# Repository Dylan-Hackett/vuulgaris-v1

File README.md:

# Vuulgaris V1

A 4-channel sample-scrubbing instrument. Long capacitive copper pads on a PCB faceplate
represent the length of a waveform; dragging a finger along a pad scrubs through the sample.
Each track carries a swappable machine that is either a sampler or a synth, with Plaits as
the synth engine.

```
[ FACEPLATE PCB ]
  4x capacitive pads, ~216mm (length follows the inter-pad gap, Q17)
  MSP430FR2675TPTR (CapTIvate touch MCU) on the back side
        |
        |  UART (primary) or I2C (fallback), + IRQ, + BSL entry lines
        v
[ MAIN PCB ]
  Daisy Patch SM (STM32H750) - audio engine, sample playback, UI
  microSD socket
  2.42" SSD1309 OLED (SPI)
  Rotary encoder
  Stereo Buchla-style low pass gate (analog)
```

## Layout

| Folder | Contents |
|---|---|
| [`docs/`](docs/) | `design-state.md` (source of truth), ADRs, open questions, pin allocation, panel budget |
| [`mockups/`](mockups/) | Parametric comb pad generator, Salamis faceplate reference + dimensioned |
| [`datasheets/`](datasheets/) | Manifest, fetch script and the datasheet PDFs. |
| [`hardware/`](hardware/) | Faceplate and main PCB, gerbers, BOM spreadsheet |
| [`fw-daisy/`](fw-daisy/) | Daisy Patch SM firmware. libDaisy + DaisySP as submodules. |
| [`fw-touch/`](fw-touch/) | MSP430FR2675 firmware. CCS + CapTIvate Design Center. |

## Start here

1. **[docs/design-state.md](docs/design-state.md)** is authoritative. Everything else is
   derived from it.
2. **[docs/notes/next-steps.md](docs/notes/next-steps.md)** step 0 is the thing to do first,
   and it is deliberately cheap: one 2-layer board with **two pads in final tooth geometry**,
   roughly $50 and 2 weeks. It answers whether a moving finger reads and repeats cleanly, and
   the second pad settles the inter-pad gap, which sets the size of the whole instrument.
3. **[docs/pin-allocation.md](docs/pin-allocation.md)** is resolved and safe to lay out
   against. Zero spare bidirectional GPIO, so any addition means a removal.
4. **[docs/panel-budget.md](docs/panel-budget.md)** is **not** settled, and it hinges on one
   measurement. The Salamis composition locks `pad length = 12 x pad pitch`, so the inter-pad
   gap ([Q17](docs/notes/open-questions.md)) sets the size of the whole instrument: a 6mm gap
   gives a 298 x 154mm panel with 216mm pads, a 10mm gap gives 365 x 189mm with 264mm pads.
5. **[docs/notes/open-questions.md](docs/notes/open-questions.md)** lists what is still
   unverified. Only one is a real design risk: **Q1**, whether a moving finger on bare copper
   reads and repeats cleanly. **Q10, Q13, Q15, Q18** are bench or datasheet checks. **Q17**
   (inter-pad gap) sets the instrument size. **Q7** is a cash decision.

## Setup

```bash
# Firmware submodules
git -C fw-daisy submodule update --init --recursive
cd fw-daisy && make libs && make

# Datasheets are committed; this re-fetches any that are missing
cd datasheets && ./fetch-datasheets.sh
```

## The three facts that shape everything else

**The MCU is on the faceplate, not the main board.** TI's design guide says keep
MCU-to-electrode traces as short as possible and explicitly warns against routing capacitive
sensing lines through board-to-board connectors or cables. That is what forces the two-board
split, and only ~8-10 digital pins cross between them.

**Accuracy is not the requirement. Monotonicity and continuity are.** You scrub by listening
and adjusting, so the loop closes through your ears and absolute position error is inaudible.
A bent curve is a lookup table. What cannot be fixed downstream is a **momentary reversal**
(sample stutters backward) or a **dropout** (click). Scan rate and jitter at rest are both
settled, see [Q1](docs/notes/open-questions.md). This is where the Trautonium pivot changed
the requirements: there, position was pitch and a 2% error was a wrong note.

**Electrode order is generated first, then laid out.** `RX0->E00, RX1->E01, RX2->E02,
RX3->E03`, produced in Design Center **before** the PCB. A swapped pair gives garbage
interpolation on a board that passes every electrical check.

**Every pot past the eighth costs a bidirectional GPIO.** CV_1-CV_8 are input-only pins that
can do nothing else, so the first 8 are free. Pots 9-12, the envelope attack and release for
each stereo side, take A2, A3, D8 and D9, and that consumes all 16 bidirectional GPIO exactly.
A 13th is impossible.

**Patch SM has two USB ports, and only one of them is on the header.** DFU flashing and USB
MIDI run on the module's own onboard Micro USB (PA11/PA12). **A8/A9 are a separate USB host
port**, spent here on IO. The cost is that USB access means unscrewing the module from the
rack; firmware ships via SD card instead.

## Decisions already made

| # | Decision |
|---|---|
| [0001](docs/decisions/0001-pivot-to-capacitive-scrubbing.md) | Pivot from Trautonium analog to capacitive sample-scrubbing |
| [0002](docs/decisions/0002-msp430fr2675-for-touch.md) | MSP430FR2675 (CapTIvate) for touch sensing |
| [0003](docs/decisions/0003-comb-pad-rx0-wraparound.md) | Comb-tooth pads with RX0 wraparound |
| [0004](docs/decisions/0004-no-overlay-exposed-copper.md) | Exposed copper, no overlay, ENIG |
| [0005](docs/decisions/0005-bsl-over-daisy-uart.md) | Daisy flashes the MSP430 over BSL |
| [0006](docs/decisions/0006-ssd1309-oled.md) | 2.42" SSD1309 over SPI |
| [0007](docs/decisions/0007-buchla-lpg-over-serge-vcfq.md) | Buchla-style LPG, not Serge VCFQ |
| [0008](docs/decisions/0008-boot-sram-not-qspi.md) | BOOT_SRAM, QSPI reserved for samples |
| [0009](docs/decisions/0009-io-plan-12-adc.md) | IO plan: 12 ADC, no mux, 1-bit SD, no panel USB |

## Cost

**$162.40 at qty 1** per [the BOM](hardware/bom/vuulgaris-v1-bom.xlsx), of which **$48.76 is
confirmed** against real listings and the rest is estimated. Inside the $125-200 range in
design-state section 10.

**The enclosure is not in that number.** The prior design was CNC walnut. It is cost lever
number 3 and currently unbounded.

Stock warnings that matter: **MSP430FR2675 has 10 units at LCSC**, and the **SSD1309 has 27**.
Both are prototype quantities.

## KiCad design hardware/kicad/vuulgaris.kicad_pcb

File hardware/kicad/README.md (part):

# Vuulgaris V1 — KiCad project (main PCB)

**Migrated from EasyEDA 2026-08-16.** Schematic connectivity is generated from a
declarative netlist and verified against KiCad's own netlister. Requires KiCad 7.

```
vuulgaris.kicad_sch   69 components, 217 connections, 66 nets — VERIFIED 217/217
vuulgaris.kicad_pcb   284.3 x 125.0mm on Edge.Cuts
lib/                  symbols + footprints (see below)
tools/                the generator and the netlist it generates from
```

## Why this exists

The EasyEDA version was abandoned after its API repeatedly reported success for
writes it had not performed — `deleteBoard` returning true having deleted nothing,
`importChanges` returning true and doing nothing, wires created at exact pin
coordinates that the netlister then refused to bind. It produced a board where
**`P3V3_DAISY` was shorted to `I2C_SDA` across 9 pads** and both LDO outputs sat on
GND, and no ERC would flag any of it, because every one of those is an electrically
legal connection. It was only ever caught by diffing pad nets against an explicit
intended map.

KiCad's design is a text file. A write either happens or raises. That is the whole
reason for the move.

## The verification loop

This is the thing worth preserving. `tools/netmap.json` is the **intent**: every
pin that carries a net, taken from `docs/pin-allocation.md`. The check is:

```bash
python3 tools/mksch.py && python3 tools/netcheck.py
```

`mksch.py` is the drawing engine; the design it draws — which symbol each ref uses,
where it sits on the sheet, which footprint it gets — is `tools/design.py`. They were
one file until 2026-09-27, when the faceplate needed the same engine. The loop tools
(`mksch`, `netcheck`, `drc`, `boardcheck`, `ksym`) all take `--project faceplate`;
`tools/proj.py` says where each project keeps what.

`netcheck.py` exports the netlist with `kicad-cli` — KiCad's own code, not a
reimplementation — and diffs every `(ref, pin) -> net` both ways. The reverse
direction is the one that matters: a pin KiCad bound to a net that `netmap.json`
never asked for is exactly the `P3V3_DAISY`-shorted-to-`I2C_SDA` failure above,
and no ERC will ever flag it. **Re-run it after any change.**

Then, before plotting fab files:

```bash
python3 tools/place.py --check && python3 tools/gerbercheck.py
```

And the one that has the last word on clearance:

```
python3 tools/drc.py
```

`drc.py` runs **KiCad's own DRC** through `pcbnew.WriteDRCReport`, because
`kicad-cli` in 7.0.8 cannot. It fails on anything the project settings call an
ERROR and merely counts WARNINGs, of which this board has ~270 silkscreen ones
that JLC clips at plot time.

`boardcheck.py` is still worth running — it is fast and it checks parity
against `netmap.json`, which DRC knows nothing about — but it is no longer the
authority on clearance. It reimplemented the geometry and got the X-crossing
case wrong, so two tracks lying on top of each other on `/LPG_LED` and
`/LPG_LEDK` measured 0.6mm apart and it reported the board clean for days.
Pcbnew found them in a second.
```

## Libraries

| Library | Source | Notes |
|---|---|---|
| `lib/vuulgaris.kicad_sym` + `.pretty` | `easyeda2kicad` from LCSC part numbers | Same geometry as the EasyEDA parts, not a reinterpretation |
| `lib/daisy_es.kicad_sym` | [GregBurns/sm_kicad](https://github.com/GregBurns/sm_kicad) | Daisy Patch SM **plus** a Eurorack kit — jacks, toggles, pots, LEDs, power symbols |

Adding a part:

```bash
easyeda2kicad --full --output lib/vuulgaris --lcsc_id CXXXXXXX
```

**The Daisy symbol here has all 40 pins including A7 (GND).** The EasyEDA community
symbol was missing A7 entirely, which passes ERC silently — a pin that does not
exist cannot be reported unconnected. That defect does not exist in this project.

**Footprint format caveat:** easyeda2kicad writes the legacy `(module ...)` form.
KiCad converts it correctly when loading from the library, but it cannot be pasted
raw into a `.kicad_pcb`. Pull footprints in via Update PCB from Schematic, not by
editing the board file.

## Placement

Two kinds of position, governed differently:

| | Governed by | Move it in Pcbnew? |
|---|---|---|
| **Panel parts** (20) | the faceplate artwork | reverted, and reported — a knob has to come through its hole |
| **Free parts** (23) | you | kept. `place.py` re-reads them every run |

So: **drag the free parts around in Pcbnew, save, and they stay put.** Their
positions are recorded in `tools/free-placement.json` so the layout shows up in a
diff. A part missing from that file is new — it just arrived via F8 — and gets
seeded once from `FREE_SEED`, then the board owns it. `--reset` throws away free
moves and goes back to the seed.

Panel-facing parts are **derived, not chosen** — their coordinates come from
`hardware/placement-panel-facing.txt`, itself generated by
`mockups/generate-faceplate.py --placement`. KiCad PCB space is Y-down and native
millimetres, the same convention as that file, so the only transform is the origin
shift:

```
pcb_mm = panel_mm - (6.995, 7.000)
```

**Footprint origin is not the shaft.** What must line up with a faceplate hole is
the shaft axis, and for three of these parts that sits away from the origin:

| Part | Footprint | Shaft / centre at | Evidence |
|---|---|---|---|
| ENC1-ENC10 | `SW-TH_EC12EXXXX` | `(0, -3.75)` | silk body centre **and** both mounting lugs |
| ENC0 | `SW-TH_ALPS_EC11L1525G01` | `(0, -0.20)` | bushing circle r 4.00 |
| RV1-RV6 | `RES-ADJ-TH_RK09L1240A12` (dual-gang, Alpha `RD902F` fitted) | `(0, -5.00)` — but **placed** at `(0, -4.83)`, see `place.py` | on the tab-slot line: the ALPS RK09L and Alpha RD902F drawings |
| SW4-SW9 | `KEY-TH_4P-L12.0-W12.0-P5.00-LS12.5` (12x12 tactile) | `(0, 0)` | pads symmetric about the origin |
| DS1 | `LCD-TH_HS242L01W4S01` | header, mid of the left edge | (folded into `PANEL`) |

Placing those by origin puts the knob 4-5mm off its hole, which nothing downstream
would flag. `ORIGIN_OFFSET` in `place.py` carries the correction.

**Only ENC0 and the pots have a bushing circle to key off.** The EC12 has none —
its only circles are four r=0.9 pad drill markers, and treating the largest of
those as a shaft puts the part 4.1 x 5.1mm out. Infer the shaft from the largest
circle *above r 1.5*, the silk body centre, and the largest pad, and accept the
part if **any** of them lands on the hole. That is what `place.py` does.

Because `ORIGIN_OFFSET` is an input, checking board positions back against the
panel file cannot validate it -- both sides use the same table, so a wrong value
passes in both directions. `place.py` therefore re-derives each shaft from the
footprint's own geometry and reports disagreement. That check is what caught
ENC1-ENC10 sitting 3.75mm high after they had already been committed and pushed.

`place.py` also reports **footprint overlaps**, bounding each part by its own pad
and outline geometry. No ERC or DRC catches a part sitting on another at this
stage, and it already caught U5 landing on ENC6.

## Editing protocol

> **This has now cost real work four times.** Pcbnew's in-memory snapshot has
> overwritten placement twice, the whole headphone block once, and -- worst --
> silently restored a **damaged board outline** after it had been repaired on
> disk. Close it.

KiCad holds the design in memory and both **F8 and Save read from that snapshot,
not from disk.** An Eeschema window left open while these tools run will silently
overwrite them on its next save, and F8 from a stale window reports "no changes"
for edits that are sitting on disk. **Close Eeschema and Pcbnew between hand-offs.**

### pose.py -- F8 does not remember which SIDE a part is on

`place.py` owns X/Y. It does **not** own layer or rotation, because those live only
in the board file. So every F8 that re-imports a footprint drops it back on `F.Cu`
at 0 degrees, and the work of flipping a block to the back is gone. **This has
happened three times:** the bypass caps, then the entire headphone block, twice.

`pose.py` is the other half. It snapshots layer+rotation for all 295 parts (160 of
which are not `F.Cu`/0) and puts them back:

```
python3 tools/pose.py --save     snapshot what the board currently is
python3 tools/pose.py --check    report what drifted, write nothing
python3 tools/pose.py            put it back
```

**Order after an F8:** `place.py` -> `pose.py` -> `place.py --check`.

A pad's angle in the file is **absolute** -- the footprint rotation is already
folded in -- so turning a footprint means rewriting every pad angle. `pose.py`
recovers the relative angle from the board's own current pose rather than from the
library, because the library lookup is keyed on pad coordinates that do not always
match, and a miss there invents a rotation out of nothing. That is what put 270 on
J9's oval pads, which carry none. Verified by clobbering all 160 posed parts to
`F.Cu`/0 and restoring: byte-identical except for the silkscreen note below.

> **That silkscreen note was the tip of a real bug.** Back-side text missing
> `(justify mirror)` turned out to correlate perfectly with footprints that had
> been moved to `B.Cu` by rewriting layer names and nothing else. See below.

## A B.Cu footprint has to be MIRRORED, not just relabelled

**KiCad applies no implicit mirror.** Proven 2026-09-09 with `kicad-cli pcb export
svg`: a pad at footprint-local `(0, +3)` plots to the *same absolute place* whether
its footprint sits on `F.Cu` or `B.Cu`. Front and back render identically.

So the flip has to be **baked into the stored coordinates**. A part on the back
carries negated local Y; a part whose coordinates still match the library is not
flipped, it is the **front land pattern printed on the back layer** -- pin 1 where
pin 8 belongs, chip soldered mirror-image.

**Thirteen parts were in that state**, and they were not minor ones:

`Q1`, `Q2`, `U101`, `U102`, `U103`, `U104`, `U106`, `U201`, `U202`, `U203`,
`U204`, `U206` -- both V3205SD bucket brigades, both CD4046 clocks, five of the
six TL072s, and both transistors. Effectively the whole analogue block. That board
would not have worked.

### Why nothing caught it

`place.py` was computing every back-side part's geometry with an extra mirror of
its own (`mir = -1.0 if side != F.Cu`), so a half-flipped part came out looking
right: two errors that cancelled inside the checks. The old comment on that line
claimed Gerber verification against J7 and J11 -- but **J7 is correctly mirrored
and J11 is on the front**, so the check compared a double mirror against a single
one and read the agreement as proof.

The tell was sitting in the same file the whole time. `place.py`'s pad-**angle**
check already assumed baked-in mirroring (`rel = -lib_angle` when on the back).
The position maths and the angle maths had contradicted each other for months.

### The guard

`place.py` now fails loudly on any `B.Cu` footprint whose asymmetric pads still
match the library. Symmetric parts (every 0603) are skipped, because for them a
Y-mirror is a no-op. Verified by deliberately half-flipping `U102` and confirming
it is named.

> Do not "flip" a footprint by editing layer strings. Use `pose.py`, which mirrors
> geometry, swaps the layer names, and mirrors the text justification together.

### The bug that pass shipped, and how it showed up

Splitting a board file into footprints by "start of one to start of the next,
with end-of-file as the last boundary" makes the **last footprint's block swallow
everything after it** -- `Edge.Cuts`, the zone, all of it. The mirror transform
then negated Y on the board outline, and the faceplate connector cutout came
apart.

The four `gr_arc` corners survived, because the negation regex wanted
`(start ...) (end ...)` adjacent and an arc carries a `(mid ...)` between them.
So the cutout lost its four straight edges and kept its four rounded corners --
which is the sort of luck that hides a bug instead of revealing it. It took
someone looking at the board to notice.

`place.py`'s `fp_blocks` had always done this correctly, walking to the balanced
closing paren. `pose.py` rolled its own and got it wrong.

**And then it came back.** The outline was repaired on disk and committed, but
Pcbnew still held the pre-fix board in memory; the next save wrote its snapshot
straight over the repair. What that looks like from the outside is an outline
that "needs to be moved" -- the parts sit at y 50-167 and the outline at y -50 to
-167, so it is drawn nowhere near the board. `place.py` now checks the outline
**before** it measures anything against it, because "pads inside the outline"
passes trivially when the outline is somewhere else entirely. **Every tool that slices
this file now ends a block at its balanced paren**, and the same bug was silently
dropping `pose.py`'s writes on three parts, which is why C505 and C511 kept
reverting to a rotation nobody asked for.

## place.py checks the board is actually THERE, and that the chip is not

Two placement mistakes got past the checks in one day, both the same shape: the
search enforced **pad**-to-pad clearance and nothing else.

**1. The board has a hole in it.** The faceplate-header cutout is 24 x 12mm at
board (210, 97.5)-(234, 109.5). "Bodies/pads inside the outline" only bounds the
board RECTANGLE, so two test points placed in the slot passed every check and were
caught by eye. `place.py` now reads interior `Edge.Cuts` loops and reports
`clear of all N board cutout(s)`.

**2. A pad can sit under a chip without touching a pad.** `V3205SD` is a DIP-14
land pattern with the middle three pins omitted on each side, so there is a wide
pad-free gap down the centre of a package that is physically still there. Two test
points landed in that gap: 2mm from any pad, and underneath the plastic. The
`body overlaps, SAME face` list already caught it -- the placement search did not,
because it only looked at pads. Searches now check **body separation as well as pad
clearance**.

The general lesson, twice over: *pads are not the part, and the outline is not the
board.*

## The courtyards in this library are FAKE -- do not trust a courtyard DRC

Every `easyeda2kicad` footprint here has its courtyard drawn as the **plastic body
outline**, which is *smaller than its own pads*:

| footprint | courtyard | pads actually reach |
|---|---|---|
| `C0603` | +/-0.80 x +/-0.40 | **+/-1.10 x +/-0.45** |
| `SOIC-8_L4.9-W3.9-P1.27-LS6.1-BL` | +/-2.50 x +/-2.00 | **+/-3.05** |

IPC says a courtyard is pads + body + margin. These are body-only. A courtyard
overlap check -- **including KiCad's own DRC** -- therefore passes a board whose
parts physically collide, and this board reports **0 courtyard overlaps** while
having had parts 0.64mm apart. That is why nothing ever complained.

**So clearance here is checked pad-to-pad in `place.py`, not by courtyard.** If you
ever run KiCad's DRC, its courtyard result means nothing until the library is
fixed.

## Crowding: overlap is not the only failure

`place.py` reports the **tightest pad-to-pad clearance on the board** and lists
everything under 1.0mm. Being on the same net earns a part nothing here — the
connection is made by copper, not by proximity, and a 0603 sitting 0.3mm off a
SOIC pin passes every overlap check while still being impossible to rework.

JLC's assembly floor is ~0.2mm, but that is a *fabrication* limit, not a working
clearance, so the check warns at **1.0mm** and only fails under **0.45mm**.

Current tightest, all understood:

| gap | pair | why |
|---|---|---|
| 0.80mm | SW4/5, SW6/7, SW8/9 | the button column pitch. 14.7mm shorts outright, 15.5mm leaves 0.8mm — a deliberate floor, and they are through-hole so hand-solderable |
| 0.82mm | DS1 x J1 | pre-existing, OLED header against the SD socket |
| 0.95mm | TP8/10/11/12 | test points, placed to 0.4mm search clearance |

The 24 bypass caps used to sit at **0.64mm** — I put them there chasing short
decoupling paths and it was too tight to get an iron in. Re-placed against a
**1.0mm pad-to-pad floor**; the cost was almost nothing, 2.1-3.1mm from the power
pin became 2.4-3.2mm.

## The LPG trimmers are SMD and live on the BACK

`RT301`/`RT401` are **3224W-1-203E**, LCSC **C55071** -- the SMD sibling of the
Bourns 3266W they replaced: same 4mm square multiturn cermet, **12 turns**,
top-adjust. Footprint pulled with `easyeda2kicad`, same as every other part here.

**Multiturn is not optional.** These set the vactrol LED drive depth, which is
adjusted by ear against a scope at bring-up. The 3x3mm single-turn parts on LCSC
are cheaper and better stocked, but they put the whole 20k into 270 degrees.

**They sit on `B.Cu` while the rest of the LPG is on `F.Cu`.** The front is under
the faceplate, so a top-adjust trimmer there is only reachable with the panel off.
Vactrols age -- and these are the Xvive reissue with known batch spread -- so
re-trimming is a real event, not a one-off.

Swapping this also took two parts off the hand-solder list. What is left there is
genuinely unsourceable rather than merely inconvenient: `V3205SD` x2, `VTL5C3` x4,
the DW3 switches x2, and the Daisy module.

> **Changing a footprint needs more than F8.** "Update PCB from Schematic" only
> syncs nets and adds/removes parts by default; a footprint swap on an
> already-placed component is opt-in. Tick **"Replace footprints with those
> specified in the schematic"** or nothing happens -- silently, with the dialog
> reporting success.

## Input level: the 1/4" jacks are a LINE input, and were wired at unity

`J7`/`J8` fed `U1.B3/B4` through nothing but a coupling cap. The Patch SM's full
scale is Eurorack 9.5Vpp = 3.36Vrms, so a normal source lands well short:

| source | nominal | at unity |
|---|---|---|
| receiver / RCA line out | 0.32Vrms | **-20.5dBFS** |
| phone or laptop headphone out, full | ~1.0Vrms | **-10.5dBFS** |
| pro +4dBu | 1.23Vrms | -8.7dBFS |

**Software gain does not fix this.** Digital gain lifts the converter's own noise
floor with the signal; 20dB below full scale is 20dB of ADC dynamic range already
gone. Only analogue gain ahead of the ADC gets it back.

Worth being explicit about why this is a line input and not a Eurorack one: **audio
I/O is PJ-603 (1/4"), CV is PJ-376 (3.5mm).** Nothing Eurorack arrives at J7/J8
without an adapter, so there was never a reason to calibrate them for 9.5Vpp.

### U10, and where it sits

```
J7 tip --R517 1k-- C511 1uF --+-- U10A +        gain = 1 + RT503/R521
                            R519 100k                = 1x to 10.1x  (0 to +20dB)
                              GND
                   U10A - --+-- R521 2k2 -- GND
                            +-- RT503 20k rheostat -- U10A out
                   U10A out -+-- C501 1uF -- SW2.1
                              +-- R302 10k -- LPG input mix (C306)     since 2026-09-25
```

**U10 also drives the LPG directly** (ADR 0011): its output is mixed with the Daisy's into
the LPG input through `R302`/`R402`, so external audio reaches the analog chain with no
conversion and can be resampled after the effects in one pass. `C306`/`C406` block its DC
there, as `C501` does on the way to the Daisy.

**Before SW2, on the EXT branch only** -- the resample path is already at Eurorack
level and must not be gained.

- `U10` is a second **OPA1688**, the same part and footprint as U9. No new library work.
- `RT503`/`RT504` are the same **3224W** 12-turn as every other trim here, on `B.Cu`.
  Wiper tied to one end, as `RT301` is: a wiper fault then gives maximum resistance
  rather than an open feedback loop.
- At minimum the trimmer is 0R and the stage is a unity follower, so a hot source
  is still safe.
- `C501` already blocks DC into SW2, so U10's offset never reaches the Patch SM and
  the feedback leg needs no cap of its own.
- `R519` 100k sets the input impedance -- a proper bridging load -- and gives 1.6Hz
  with `C511`.
- `R517`/`R518` 1k are series protection. There was none: `C501` went straight onto
  a module pin, and a source peaking at +18dBu is 17.4Vpp against a +/-4.75V input.
  Against 100k the 1k costs under 0.1dB.

## The audio coupling caps are 0805, and they were never going to be film

Fourteen caps carried the value **"1uF film" in an 0603 footprint**. That is not a
part anyone can ship. SMD film tops out around **0.1uF** (PPS, Panasonic ECHU) in
1210; 1uF film means a leaded box cap about 7x7mm on a 5mm pitch -- through-hole,
hand-soldered, on a board whose hand-solder list was deliberately cut down to four
genuinely unsourceable parts. Whatever got assembled was always going to be a
Class II MLCC, and the value string was describing a wish.

`C113 C120 C213 C220 C306 C406 C501 C502 C503 C504 C505 C506 C511 C512`
-> **1uF X7R 50V, C0805.**

**Why 0805 and 50V rather than just renaming them.** Class II voltage-coefficient
distortion scales with the field across the dielectric. A 1uF 50V part in 0805 has
more and thicker layers than a 1uF 16V part in 0603, so on a **+/-4.75V Eurorack
signal** -- nearly a third of a 16V part's rating -- it distorts substantially
less for the same job. Same money, same reel, same pick-and-place.

**1uF C0G would be genuinely linear and is not an option**: it does not exist below
2220, runs a few dollars each, and fourteen of them would cost more than the rest
of the passives put together and swallow the board.

Eleven of the fourteen took the bigger footprint where they stood. `C505` turns 90
degrees to clear J6's body, `C511` moves 3.4mm, `C512` 0.25mm.

> **This one needs the checkbox.** A footprint swap on an already-placed part is
> opt-in: tick **"Replace footprints with those specified in the schematic"** in
> the F8 dialog or nothing happens, silently, with the dialog reporting success.

## Output levels: three different jobs, three different levels

Everything inside the instrument runs at **Eurorack level, 9.5Vpp (+/-4.75V)** --
verified from the Patch SM datasheet v1.0.5, which benchmarks SNR against exactly
that reference sine. Bergman's LPG expects the same, so `AUDIO_OUT -> LPG ->
AUDIO_IN` is level-matched end to end. See `docs/design-state.md` section 6.

`BBD_OUT_L/R` is that node. **Three things hang off it, and only one of them wants
Eurorack level:**

```
U103 --470R(R131)-- BBD_OUT_L --+-- C503 1u ---- SW2 -- AUDIO_IN_L    9.5Vpp, internal
                                |
                                +-- C505 1u -- R509 100k -+- RT501 20k -- GND
                                |                    wiper |
                                |                          U9 (unity) --4R7-- J6 tip
                                |
                                +-- R513 1k2 --+-- J9 tip   (1/4" line out)
                                              R514 1k
                                               GND
```

**The attenuators sit DOWNSTREAM of the C503 and C505 taps.** That is the whole
trick, and it is the reason nothing internal had to change: the resample loop and
the headphone feed still see the Eurorack level they were designed around, while
the jack sees whatever the divider gives it.

*Nearly* that level: the taps are on the far side of `R131`, and the line-out
divider loads that node with 2.2k, so `BBD_OUT` sits at 2200/2670 = 0.82 of
U103's swing, **-1.7dB**. The resample path reaches the Patch SM about 2dB under
full scale instead of at it. Harmless, but it is not the unloaded buffer level.

### 1/4" line out (J9/J10) -- +4.2dBu full scale

`R131` 470R is already in series, so the divider is **(470 + 1200) : 1000**.
(`R513`/`R515` are 1k2 on the board. This section was written for 1k3; the
numbers below are for 1k2, 0.3dB hotter.)

| | |
|---|---|
| ratio | 1000/2670 = 0.375, **-8.53dB** |
| full scale | 3.359Vrms -> **1.258Vrms = +4.2dBu** |
| output impedance | 1670 \|\| 1000 = **625R** |
| load on U103 | 2670R -- a TL072 is rated to 2k, so this is inside spec |

It was **+12.7dBu** before, straight off the buffer. That survives a pro interface
(+18 to +24dBu max) but clips consumer -10dBV gear and anything with an instrument
input. +4.2dBu is safe everywhere and still hot enough to ignore the noise floor:
625R of thermal noise is 3.2nV/sqrt(Hz), about **-125dBu** over 20kHz.

Passive is the right answer here -- U103 already buffers the node, so a divider
costs two 0603s and no active parts. Into a 10k line input you lose another 0.5dB.
Into a 600R vintage input you lose 6.2dB, which is the one case worth knowing about.

### Headphones (J6) -- set once, on the back

`RT501`/`RT502` are the same **3224W** 12-turn cermet as the LPG trimmers, on
`B.Cu` for the same reason. Max attenuation is 20k/120k = 1/6, giving **0.56Vrms**
at the buffer output.

> **U9's own bypass caps were 15mm away, and nothing was checking.** `C507`/`C508`
> were never in `place.py`'s `BYPASS` table, so the headphone driver shipped with
> decoupling that was decoration -- the trace inductance in series with a 100nF at
> that distance undoes most of what it is for. Adding U9 and U10 to the table
> caught it immediately; `RT502` had to move 7.5mm off pin 8 to free the pocket.
> **Every chip with a bypass cap belongs in that table**, or the check is only
> auditing the parts that were already right.

`R511`/`R512` are **4R7, not 22R.** They sit OUTSIDE the feedback loop -- U9's
feedback comes off `HP_BUF_L`, before them -- so they set output impedance directly:

| load | with 22R | with 4R7 |
|---|---|---|
| 32R | 0.332Vrms, 3.4mW | **0.488Vrms, 7.4mW** |
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
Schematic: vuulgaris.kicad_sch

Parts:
C20, C22, C24, C25, C29: CL21A106KAYNNNE; C0805
C21, C23, C26, C27, C44: CL05B104KO5NNNC; C0402
C28: CC0603JRNPO9BN103; C0603
C30: CC0805KKX7R9BB105; C0805
C31, C34, C35, C38, C39, C43: CC0603JRX7R8BB104; C0603
C32, C33: RVT1E470M0505_C2977553; CAP-SMD_BD5.0-L5.3-W5.3-LS6.3-FD
C36, C37: RVT1H220M0605; CAP-SMD_BD6.3-L6.6-W6.6-FD
C40, C41, C105, C106, C107, C108, C109, C111, C121, C122, C205, C206, C207, C208, C209, C211, C221, C222, C301, C302, C303, C304, C401, C402, C403, C404, C507, C508, C509, C510: 100nF; C0603
C42, C110, C210: 10uF; C0805
C113, C120, C213, C220, C306, C406, C501, C502, C503, C504, C505, C506, C511, C512: 1uF X7R 50V; C0805
C114, C214, C309, C409: 1nF C0G; C0603
C116, C216, C307, C407: 220pF C0G; C0603
C119, C219: 10nF C0G 0805; C0805
C305, C405: 2nF C0G; C0603
C308, C408: 4.7nF C0G; C0603
C310, C410: 22pF C0G; C0603
D1, D2: YLED0402Y; LED0402-R-RD
D3: SMAJ6.0A; SMA_L4.3-W2.6-LS5.2-RD
D103, D104, D105, D106, D107, D203, D204, D205, D206, D207, D302, D402: 1N4148W; SOD-123_L2.8-W1.8-LS3.7-RD
D301, D401: 3V9 zener; SOD-123_L2.7-W1.6-LS3.7-RD-1
DS1: HS242L01W4S01; LCD-TH_HS242L01W4S01
ENC0: EC11L1525G01; SW-TH_ALPS_EC11L1525G01
ENC1, ENC2, ENC3, ENC4, ENC5, ENC6, ENC7, ENC8: EC12E2430803; SW-TH_EC12EXXXX
F1: ASMD1812-300; F1812
FB1, FB2: BEAD0805S601A20T; R0805
J1: TFPUSH; TF-SMD_TF-PUSH
J2, J3, J4, J5, J6: PJ-376; AUDIO-TH_PJ-376
J7, J8, J9, J10: PJ-603_C41409498; AUDIO-TH_PJ-603
J11: TYPE-C-31-M-12; USB-C_SMD-TYPE-C-31-M-12_1
J12: FACEPLATE 2x5 IDC; IDC-TH_10P-P2.54_C5665
L1, L2: BLM18PG121SN1D_C14709; L0603
Q1, Q2: J113 / MMBFJ113; SOT-23-3_L2.9-W1.3-P1.90-LS2.4-BR
R20, R21: 0402WGF2201TCE; R0402
R22, R23: RT0603BRD075K1L; R0603
R24, R25: RT0603BRD072K2L; R0603
R104, R204: 0R (IN GAIN -- OPEN, see docs/bbd-mki.md); R0603
R106, R115, R116, R117, R122, R124, R125, R128, R130, R206, R215, R216, R217, R222, R224, R225, R228, R230, R305, R309, R310, R317, R318, R320, R323, R328, R330, R331, R333, R405, R409, R410, R417, R418, R420, R423, R428, R430, R431, R433, R509, R510, R519, R520: 100k; R0603
R107, R207, R315, R415, R503, R504, R514, R516, R517, R518: 1k; R0603
R110, R111, R129, R210, R211, R229: 22k; R0603
R112, R212: 82k; R0603
R113, R213, R506, R507, R508: 47k; R0603
R114, R214: 51k; R0603
R118, R126, R218, R226, R301, R302, R308, R314, R401, R402, R408, R414, R505: 10k; R0603
R119, R219: 4.7k; R0603
R120, R220: 62k; R0603
R121, R221, R334, R434: 2.2M; R0603
R123, R223: 39k; R0603
R127, R227: 6.2k; R0603
R131, R132, R231, R232, R306, R406: 470R; R0603
R303, R403: 150k; R0603
R304, R404: 470k; R0603
R307, R407: 33k; R0603
R311, R312, R411, R412: 15k; R0603
R313, R413: 4M7; R0603
R501, R502: 1M; R0603
R511, R512: 4R7; R0603
R513, R515: 1k2; R0603
R521, R522: 2k2; R0603
RT301, RT401, RT501, RT502, RT503, RT504: 20k trim; RES-ADJ-SMD_3224W
RV1: CUTOFF; RES-ADJ-TH_RK09L1240A12
RV2: RESONANCE; RES-ADJ-TH_RK09L1240A12
RV3: FILTER CV AMT; RES-ADJ-TH_RK09L1240A12
RV4: TIME; RES-ADJ-TH_RK09L1240A12
RV5: FEEDBACK; RES-ADJ-TH_RK09L1240A12
RV6: WET/DRY; RES-ADJ-TH_RK09L1240A12
SW1, SW2: SW_DPDT_FLAT; SW-TH_DW3_DPDT_2MD1T1B1M2QES
SW4, SW5, SW6, SW7, SW8, SW9: 12x12 tactile; KEY-TH_4P-L12.0-W12.0-P5.00-LS12.5
TP1: +12V; TestPoint_TH_D1.0mm
TP2: -12V; TestPoint_TH_D1.0mm
TP3: +5V; TestPoint_TH_D1.0mm
TP4: +5V BBD; TestPoint_TH_D1.0mm
TP5: GND; TestPoint_TH_D1.0mm
TP6: DRY L; TestPoint_TH_D1.0mm
TP7: DRY R; TestPoint_TH_D1.0mm
TP8: SIGIN L; TestPoint_TH_D1.0mm
TP9: SIGIN R; TestPoint_TH_D1.0mm
TP10: LED L; TestPoint_TH_D1.0mm
TP11: LED R; TestPoint_TH_D1.0mm
TP12: CLK L; TestPoint_TH_D1.0mm
TP13: CLK R; TestPoint_TH_D1.0mm
TP14: TIME CV; TestPoint_TH_D1.0mm
TP15: LPG ENV; TestPoint_TH_D1.0mm
U1: ES_DAISY_PATCH_SM_REV1; DAISY_PATCH_SM
U3, U4: MCP23017-E_SO; SOIC-28_L18.0-W7.5-P1.27-LS10.3-BL
U5, U6: AMS1117-3.3; SOT-223-3_L6.5-W3.4-P2.30-LS7.0-BR
U7: DKM10E-12; PWRM-TH_DKMW30F-12
U8: AMS1117-5.0; SOT-223-3_L6.5-W3.4-P2.30-LS7.0-BR
U9, U10: OPA1688_FLAT; SOP-8_L4.9-W3.9-P1.27-LS6.0-BL
U101, U201: V3205SD; DIP-8_SPECIAL_V3205SD
U102, U103, U106, U202, U203, U206: TL072_FLAT; SOIC-8_L4.9-W3.9-P1.27-LS6.1-BL
U104, U204: CD4046B; SO-16_L10.3-W5.3-P1.27-LS7.8-BL
U301, U401: TL084; SOIC-14_3.9x8.7mm_P1.27mm
U302, U402: TL074; SOIC-14_3.9x8.7mm_P1.27mm
VT301, VT302, VT401, VT402: VTL5C3; VACTROL-TH_VTL5C3

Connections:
/AUDIO_IN_L: R501.1, SW2.2 (A_COM), U1.B4 (AUDIO_IN_L)
/AUDIO_IN_R: R502.1, SW2.5 (B_COM), U1.B3 (AUDIO_IN_R)
/AUDIO_OUT_L: R301.1, R310.1, U1.B2 (AUDIO_OUT_L)
/AUDIO_OUT_R: R401.1, R410.1, U1.B1 (AUDIO_OUT_R)
/BBD_AC_L: C113.2, R124.1, U106.3 (1IN+)
/BBD_AC_R: C213.2, R224.1, U206.3 (1IN+)
/BBD_C1A_L: C114.1, U104.6 (CI(1))
/BBD_C1A_R: C214.1, U204.6 (CI(1))
/BBD_C1B_L: C114.2, U104.7 (CI(2))
/BBD_C1B_R: C214.2, U204.7 (CI(2))
/BBD_CLKN_L: U101.2 (CP2), U104.2 (PHASECOMPIOUT)
/BBD_CLKN_R: U201.2 (CP2), U204.2 (PHASECOMPIOUT)
/BBD_CLK_L: C116.1, TP12.1, U101.6 (CP1), U104.3 (COMPIN), U104.4 (VCOOUT)
/BBD_CLK_R: C216.1, TP13.1, U201.6 (CP1), U204.3 (COMPIN), U204.4 (VCOOUT)
/BBD_DRY_L: R104.1, RV6.1, TP6.1, U102.1 (1OUT), U102.2 (1IN-)
/BBD_DRY_R: R204.1, RV6.4, TP7.1, U202.1 (1OUT), U202.2 (1IN-)
/BBD_FB_L: R112.1, RV5.2
/BBD_FB_R: R212.1, RV5.5
/BBD_GAIN_L: R104.2, R114.1
/BBD_GAIN_R: R204.2, R214.1
/BBD_INF_L: R107.2, U102.3 (1IN+)
/BBD_INF_R: R207.2, U202.3 (1IN+)
/BBD_INH_L: D104.2 (A), D106.1 (K), R117.2, U104.5 (INHIBIT)
/BBD_INH_R: D204.2 (A), D206.1 (K), R217.2, U204.5 (INHIBIT)
/BBD_IN_L: R106.1, R107.1, R315.2
/BBD_IN_R: R206.1, R207.1, R415.2
/BBD_MIXW_L: RV6.2, U103.5 (2IN+)
/BBD_MIXW_R: RV6.5, U203.5 (2IN+)
/BBD_MIX_L: R131.1, U103.6 (2IN-), U103.7 (2OUT)
/BBD_MIX_R: R231.1, U203.6 (2IN-), U203.7 (2OUT)
/BBD_OUT_L: C503.1, C505.1, R131.2, R513.1
/BBD_OUT_R: C504.1, C506.1, R231.2, R515.1
/BBD_RAW_L: C113.1, R122.1, U101.4 (OUT2)
/BBD_RAW_R: C213.1, R222.1, U201.4 (OUT2)
/BBD_SH_FB_L: R129.1, R130.1, U106.6 (2IN-)
/BBD_SH_FB_R: R229.1, R230.1, U206.6 (2IN-)
/BBD_SH_G_L: D107.2 (A), Q1.3 (G), R128.2
/BBD_SH_G_R: D207.2 (A), Q2.3 (G), R228.2
/BBD_SH_HOLD_L: C119.1, Q1.2 (S), U106.5 (2IN+)
/BBD_SH_HOLD_R: C219.1, Q2.2 (S), U206.5 (2IN+)
/BBD_SH_IN_L: Q1.1 (D), R128.1, U106.1 (1OUT), U106.2 (1IN-)
/BBD_SH_IN_R: Q2.1 (D), R228.1, U206.1 (1OUT), U206.2 (1IN-)
/BBD_SIGIN_L: R118.2, TP8.1, U101.7 (IN), U103.1 (1OUT)
/BBD_SIGIN_R: R218.2, TP9.1, U201.7 (IN), U203.1 (1OUT)
/BBD_SUM_L: R112.2, R113.2, R114.2, R118.1, U103.2 (1IN-)
/BBD_SUM_R: R212.2, R213.2, R214.2, R218.1, U203.2 (1IN-)
/BBD_TIMEHI_L: R110.2, RV4.1
/BBD_TIMEHI_R: R210.2, RV4.4
/BBD_TIMELO_L: R111.1, RV4.3
/BBD_TIMELO_R: R211.1, RV4.6
/BBD_TIMEW_L: R115.1, RV4.2
/BBD_TIMEW_R: R215.1, RV4.5
/BBD_TRIGIN_L: C116.2, R127.1, U102.5 (2IN+)
/BBD_TRIGIN_R: C216.2, R227.1, U202.5 (2IN+)
/BBD_TRIGREF_L: R125.2, R126.1, U102.6 (2IN-)
/BBD_TRIGREF_R: R225.2, R226.1, U202.6 (2IN-)
/BBD_TRIG_L: D107.1 (K), U102.7 (2OUT)
/BBD_TRIG_R: D207.1 (K), U202.7 (2OUT)
/BBD_VCOCV_L: D103.2 (A), D105.1 (K), R115.2, R116.2, U104.9 (VCOIN)
/BBD_VCOCV_R: D203.2 (A), D205.1 (K), R215.2, R216.2, U204.9 (VCOIN)
/BBD_VCOR1_L: R123.1, U104.11 (R1TOVSS)
/BBD_VCOR1_R: R223.1, U204.11 (R1TOVSS)
/BBD_VCOR2_L: R121.1, U104.12 (R2TOVSS)
/BBD_VCOR2_R: R221.1, U204.12 (R2TOVSS)
/BBD_VGG_L: C110.1, R119.2, R120.1, U101.8 (VGG)
/BBD_VGG_R: C210.1, R219.2, R220.1, U201.8 (VGG)
/BBD_WETAC_L: C120.2, R132.1, RV5.3, RV6.3
/BBD_WETAC_R: C220.2, R232.1, RV5.6, RV6.6
/BBD_WETOUT_L: R132.2
/BBD_WETOUT_R: R232.2
/BBD_WET_L: C120.1, R130.2, U106.7 (2OUT)
/BBD_WET_R: C220.1, R230.2, U206.7 (2OUT)
/BTN1: SW4.3, U4.25 (GPA4)
/BTN2: SW5.3, U4.26 (GPA5)
/BTN3: SW6.3, U4.27 (GPA6)
/BTN4: SW7.1, U4.7 (GPB6)
/BTN5: SW8.3, U4.21 (GPA0)
/BTN6: SW9.1, U4.22 (GPA1)
/CC1: J11.A5 (CC1), R22.1
/CC2: J11.B5 (CC2), R23.2
/CVOUT_JACK: J2.3, R503.2
/CV_IN_JACK: J4.3, U1.C9 (CV8)
/ENC0_A: ENC0.A, U4.1 (GPB0)
/ENC0_B: ENC0.B, U4.2 (GPB1)
/ENC0_PUSH: ENC0.D, U4.3 (GPB2)
/ENC1_A: ENC1.A, U3.21 (GPA0)
/ENC1_B: ENC1.B, U3.22 (GPA1)
/ENC2_A: ENC2.A, U3.23 (GPA2)
/ENC2_B: ENC2.B, U3.24 (GPA3)
/ENC3_A: ENC3.A, U3.25 (GPA4)
/ENC3_B: ENC3.B, U3.26 (GPA5)
/ENC4_A: ENC4.A, U4.23 (GPA2)
/ENC4_B: ENC4.B, U4.24 (GPA3)
/ENC5_A: ENC5.A, U3.1 (GPB0)
/ENC5_B: ENC5.B, U3.2 (GPB1)
/ENC6_A: ENC6.A, U3.3 (GPB2)
/ENC6_B: ENC6.B, U3.4 (GPB3)
/ENC7_A: ENC7.A, U3.5 (GPB4)
/ENC7_B: ENC7.B, U3.6 (GPB5)
/ENC8_A: ENC8.A, U4.5 (GPB4)
/ENC8_B: ENC8.B, U4.6 (GPB5)
/EXT_AMP_IN_L: C511.2, R519.1, U10.3 (1IN+)
/EXT_AMP_IN_R: C512.2, R520.1, U10.5 (2IN+)
/EXT_AMP_OUT_L: C501.1, R302.1, RT503.1, U10.1 (1OUT)
/EXT_AMP_OUT_R: C502.1, R402.1, RT504.1, U10.7 (2OUT)
/EXT_FB_L: R521.1, RT503.2 (WIPER), RT503.3, U10.2 (1IN-)
/EXT_FB_R: R522.1, RT504.2 (WIPER), RT504.3, U10.6 (2IN-)
/EXT_IN_L: J7.4, R517.1
/EXT_IN_R: J8.4, R518.1
/EXT_PROT_L: C511.1, R517.2
/EXT_PROT_R: C512.1, R518.2
/GATEOUT_JACK: J3.3, R504.2
/GATE_IN: J5.3, U1.B10 (GATE_IN_1)
/GATE_OUT_1: R504.1, U1.B5 (GATE_OUT_1)
/GATE_OUT_2: R117.1, R217.1, U1.B6 (GATE_OUT_2)
/GND: C20.2, C21.2, C22.2, C23.2, C24.2, C25.2, C26.2, C27.2, C28.2, C29.2, C30.1, C31.1, C32.2, C33.1, C34.1, C35.2, C36.2, C37.1, C38.1, C39.2, C40.2, C41.2, C42.2, C43.2, C44.2, C105.2, C106.2, C107.2, C108.2, C109.2, C110.2, C111.2, C119.2, C121.2, C122.2, C205.2, C206.2, C207.2, C208.2, C209.2, C210.2, C211.2, C219.2, C221.2, C222.2, C301.2, C302.2, C303.2, C304.2, C307.2, C309.2, C401.2, C402.2, C403.2, C404.2, C407.2, C409.2, C507.2, C508.2, C509.2, C510.2, D1.2 (K), D2.1 (A), D3.2 (A), D105.2 (A), D106.2 (A), D205.2 (A), D206.2 (A), D301.1 (C), D401.1 (C), DS1.1 (GND), ENC0.6 (EH), ENC0.7 (EH), ENC0.C, ENC0.E, ENC1.C, ENC1.D, ENC1.E, ENC2.C, ENC2.D, ENC2.E, ENC3.C, ENC3.D, ENC3.E, ENC4.C, ENC4.D, ENC4.E, ENC5.C, ENC5.D, ENC5.E, ENC6.C, ENC6.D, ENC6.E, ENC7.C, ENC7.D, ENC7.E, ENC8.C, ENC8.D, ENC8.E, J1.6 (VSS), J1.10, J1.11, J1.12, J1.13, J2.1, J2.2, J3.1, J3.2, J4.1, J4.2, J5.1, J5.2, J6.1, J7.2, J7.3, J7.5, J8.2, J8.3, J8.5, J9.2, J9.5, J10.2, J10.5, J11.1 (EH), J11.2 (EH), J11.3 (EH), J11.4 (EH), J11.A1B12 (GND), J11.B1A12 (GND), J12.2, J12.4, J12.6, J12.8, J12.10, R22.2, R23.1, R106.2, R111.2, R120.2, R121.2, R122.2, R123.2, R124.2, R126.2, R127.2, R129.2, R206.2, R211.2, R220.2, R221.2, R222.2, R223.2, R224.2, R226.2, R227.2, R229.2, R308.2, R309.2, R310.2, R312.2, R313.2, R317.2, R318.2, R408.2, R409.2, R410.2, R412.2, R413.2, R417.2, R418.2, R501.2, R502.2, R514.2, R516.2, R519.2, R520.2, R521.2, R522.2, RT501.3, RT502.3, RV1.1, RV1.4, RV1.7, RV1.8, RV2.7, RV2.8, RV3.7, RV3.8, RV4.7, RV4.8, RV5.1, RV5.4, RV5.7, RV5.8, RV6.7, RV6.8, SW4.2, SW5.2, SW6.2, SW7.4, SW8.2, SW9.4, TP5.1, U1.A4 (GND), U1.A7 (GND), U3.8 (GPB7), U3.10 (VSS), U3.15 (A0), U3.16 (A1), U3.17 (A2), U3.28 (GPA7), U4.8 (GPB7), U4.10 (VSS), U4.16 (A1), U4.17 (A2), U4.28 (GPA7), U5.1 (GND), U6.1 (GND), U7.2 (-Vin), U7.4 (Common), U8.1 (GND), U101.1 (GND), U103.3 (1IN+), U104.8 (VSS), U201.1 (GND), U203.3 (1IN+), U204.8 (VSS), U302.3 (IN_A+), U302.5 (IN_B+), U302.10 (IN_C+), U302.12 (IN_D+), U402.3 (IN_A+), U402.5 (IN_B+), U402.10 (IN_C+), U402.12 (IN_D+)
/HP_BUF_L: R511.1, U9.1 (1OUT), U9.2 (1IN-)
/HP_BUF_R: R512.1, U9.6 (2IN-), U9.7 (2OUT)
/HP_DIV_L: R509.2, RT501.1
/HP_DIV_R: R510.2, RT502.1
/HP_IN_L: C505.2, R509.1
/HP_IN_R: C506.2, R510.1
/HP_OUT_L: J6.3, R511.2
/HP_OUT_R: J6.2, R512.2
/HP_W_L: RT501.2 (WIPER), U9.3 (1IN+)
/HP_W_R: RT502.2 (WIPER), U9.5 (2IN+)
/I2C_SCL: R20.1, U1.B7 (I2C1_SCL), U3.12 (SCL), U4.12 (SCL)
/I2C_SDA: R21.1, U1.B8 (I2C1_SDA), U3.13 (SDA), U4.13 (SDA)
/LED_NEG: D2.2 (K), R25.1
/LED_POS: D1.1 (A), R24.1
/LINE_OUT_L: J9.4, R513.2, R514.1
/LINE_OUT_R: J10.4, R515.2, R516.1
/LPG_ABUF_L: R311.1, U301.1 (OUT_A), VT301.3 (CELL1)
/LPG_ABUF_R: R411.1, U401.1 (OUT_A), VT401.3 (CELL1)
/LPG_AFB_L: R311.2, R312.1, U301.2 (IN_A-)
/LPG_AFB_R: R411.2, R412.1, U401.2 (IN_A-)
/LPG_BOUT_L: R306.1, U301.7 (OUT_B)
/LPG_BOUT_R: R406.1, U401.7 (OUT_B)
/LPG_BP_L: R308.1, U301.5 (IN_B+)
/LPG_BP_R: R408.1, U401.5 (IN_B+)
/LPG_C5_L: C305.2, R304.1
/LPG_C5_R: C405.2, R404.1
/LPG_CFB_L: R314.1, U301.9 (IN_C-)
/LPG_CFB_R: R414.1, U401.9 (IN_C-)
/LPG_CVC_L: R331.2, R333.1, U302.9 (IN_C-)
/LPG_CVC_R: R431.2, R433.1, U402.9 (IN_C-)
/LPG_CVD_L: R330.2, R331.1, U302.14 (OUT_D)
/LPG_CVD_R: R430.2, R431.1, U402.14 (OUT_D)
/LPG_CVI_L: R320.1, R323.2, U302.2 (IN_A-)
/LPG_CVI_R: R420.1, R423.2, U402.2 (IN_A-)
/LPG_CVW_L: R328.1, RV3.2
/LPG_CVW_R: R428.1, RV3.5
/LPG_CV_L: R304.2, R305.2, R333.2, U302.8 (OUT_C)
/LPG_CV_R: R404.2, R405.2, R433.2, U402.8 (OUT_C)
/LPG_ENV: R323.1, R423.1, R503.1, RV3.3, RV3.6, TP15.1, U1.C10 (CV_OUT_1)
/LPG_ENVN_L: R320.2, RV3.1, U302.1 (OUT_A)
/LPG_ENVN_R: R420.2, RV3.4, U402.1 (OUT_A)
/LPG_INF_L: C306.2, R309.1, U301.3 (IN_A+)
/LPG_INF_R: C406.2, R409.1, U401.3 (IN_A+)
/LPG_LDR_L: C309.1, R313.1, U301.10 (IN_C+), VT302.4 (CELL2)
/LPG_LDR_R: C409.1, R413.1, U401.10 (IN_C+), VT402.4 (CELL2)
/LPG_LEDD_L: D302.1 (K), R306.2
/LPG_LEDD_R: D402.1 (K), R406.2
/LPG_LEDK_L: D302.2 (A), R334.2, VT302.2 (K)
/LPG_LEDK_R: D402.2 (A), R434.2, VT402.2 (K)
/LPG_LEDM_L: VT301.2 (K), VT302.1 (A)
/LPG_LEDM_R: VT401.2 (K), VT402.1 (A)
/LPG_LED_L: D301.2 (A), R307.2, R317.1, R334.1, TP10.1, VT301.1 (A)
/LPG_LED_R: D401.2 (A), R407.2, R417.1, R434.1, TP11.1, VT401.1 (A)
/LPG_MID_L: C307.1, C308.1, VT301.4 (CELL2), VT302.3 (CELL1)
/LPG_MID_R: C407.1, C408.1, VT401.4 (CELL2), VT402.3 (CELL1)
/LPG_MIX_L: C306.1, R301.2, R302.2
/LPG_MIX_R: C406.1, R401.2, R402.2
/LPG_NC_L: U302.6 (IN_B-), U302.7 (OUT_B)
/LPG_NC_R: U402.6 (IN_B-), U402.7 (OUT_B)
/LPG_OFS_L: R303.1, RV1.2
/LPG_OFS_R: R403.1, RV1.5
/LPG_OUT_L: R314.2, R315.1, U301.8 (OUT_C), U301.12 (IN_D+)
/LPG_OUT_R: R414.2, R415.1, U401.8 (OUT_C), U401.12 (IN_D+)
/LPG_RESL_L: R318.1, RV2.3
/LPG_RESL_R: R418.1, RV2.6
/LPG_RESW_L: C310.1, RV2.2, U301.13 (IN_D-)
/LPG_RESW_R: C410.1, RV2.5, U401.13 (IN_D-)
/LPG_RES_L: C310.2, RV2.1, SW1.1 (A_NC), U301.14 (OUT_D)
/LPG_RES_R: C410.2, RV2.4, SW1.4 (B_NC), U401.14 (OUT_D)
/LPG_SUMCV_L: R328.2, R330.1, U302.13 (IN_D-)
/LPG_SUMCV_R: R428.2, R430.1, U402.13 (IN_D-)
/LPG_SUM_L: C305.1, R303.2, R305.1, RT301.1, U301.6 (IN_B-)
/LPG_SUM_R: C405.1, R403.2, R405.1, RT401.1, U401.6 (IN_B-)
/LPG_T1_L: R307.1, RT301.2 (WIPER), RT301.3
/LPG_T1_R: R407.1, RT401.2 (WIPER), RT401.3
/LPG_VCFSW_L: C308.2, SW1.2 (A_COM)
/LPG_VCFSW_R: C408.2, SW1.5 (B_COM)
/MSP430_RXD: J12.5, U1.A3 (UART_TX)
/MSP430_TXD: J12.7, U1.A2 (UART_RX)
/MSP_RST: J12.3, U4.4 (GPB3)
/MSP_TEST: J12.1
/NEG12V: C37.2, C39.1, C106.1, C108.1, C122.1, C206.1, C208.1, C222.1, C302.1, C304.1, C402.1, C404.1, C508.1, C510.1, L2.2, R25.2, R113.1, R213.1, TP2.1, U1.A1 (-12V), U9.4 (V-), U10.4 (V-), U102.4 (V-), U103.4 (V-), U106.4 (V-), U202.4 (V-), U203.4 (V-), U206.4 (V-), U301.11 (V-), U302.11 (V-), U401.11 (V-), U402.11 (V-)
/NEG12V_RAW: C33.2, C35.1, L2.1, U7.5 (-Vout)
/OLED_CS: DS1.7 (CS1), U1.D1 (SPI_NSS)
/OLED_DC: DS1.6 (DC), U1.D2 (SDMMC_D3)
/OLED_FONTCS: DS1.9 (CS2), R505.1
/OLED_MOSI: DS1.4 (SDA), U1.D9 (SPI_MOSI)
/OLED_RES: DS1.5 (RES), U1.A9 (USB_DP)
/OLED_SCK: DS1.3 (SCL), U1.D10 (SPI_SCK)
/P3V3_DAISY: C26.1, C27.1, C44.1, J1.4 (VDD), R20.2, R21.2, R506.2, R507.2, R508.2, U1.A10 (+3V3), U3.9 (VDD), U3.18 (~RESET), U4.9 (VDD), U4.15 (A0), U4.18 (~RESET)
/P3V3_MSP430: C22.1, C23.1, J12.9, U6.2 (VOUT), U6.4 (VOUT)
/P3V3_OLED: C20.1, C21.1, DS1.2 (VCC), R505.2, U5.2 (VOUT), U5.4 (VOUT)
/P5V: FB1.1, FB2.1, TP3.1, U1.A6 (+5V)
/P5V_BBD: C41.1, C42.1, C109.1, C111.1, C209.1, C211.1, D103.1 (K), D104.1 (K), D203.1 (K), D204.1 (K), R119.1, R219.1, TP4.1, U8.2 (VOUT), U8.4 (VOUT), U101.5 (VDD), U104.14 (SIGNALIN), U104.16 (VDD), U201.5 (VDD), U204.14 (SIGNALIN), U204.16 (VDD)
/P5V_MSP: C25.1, FB2.2, U6.3 (VIN)
/P5V_OLED: C24.1, FB1.2, U5.3 (VIN)
/POS12V: C36.1, C38.2, C40.1, C105.1, C107.1, C121.1, C205.1, C207.1, C221.1, C301.1, C303.1, C401.1, C403.1, C507.1, C509.1, L1.2, R24.2, R110.1, R125.1, R210.1, R225.1, RV1.3, RV1.6, TP1.1, U1.A5 (+12V), U8.3 (VIN), U9.8 (V+), U10.8 (V+), U102.8 (V+), U103.8 (V+), U106.8 (V+), U202.8 (V+), U203.8 (V+), U206.8 (V+), U301.4 (V+), U302.4 (V+), U401.4 (V+), U402.4 (V+)
/POS12V_RAW: C32.1, C34.2, L1.1, U7.3 (+Vout)
/SD_CLK: J1.5 (CLX), U1.D6 (SDMMC_CK)
/SD_CMD: J1.3 (CMD), R506.1, U1.D7 (SDMMC_CMD)
/SD_D0: J1.7 (DAT0), R507.1, U1.D5 (SDMMC_D0)
/SD_DAT3: J1.2 (CD/DAT3), R508.1
/SRC_EXT_L: C501.2, SW2.1 (A_NC)
/SRC_EXT_R: C502.2, SW2.4 (B_NC)
/SRC_RSMP_L: C503.2, SW2.3 (A_NO)
/SRC_RSMP_R: C504.2, SW2.6 (B_NO)
/TIME_CV: R116.1, R216.1, TP14.1, U1.C1 (CV_OUT_2)
/VBUS: C28.1, C43.1, D3.1 (C), F1.1, J11.A4B9 (VBUS), J11.B4A9 (VBUS)
/VBUS_F: C29.1, C30.2, C31.2, F1.2, U7.1 (+Vin)

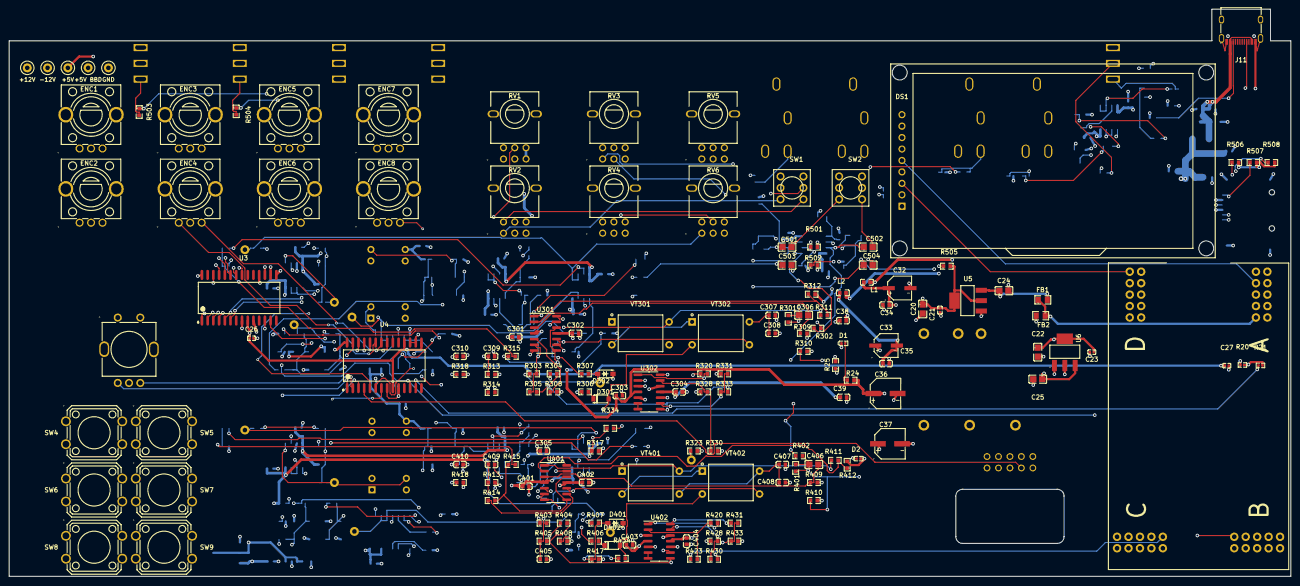
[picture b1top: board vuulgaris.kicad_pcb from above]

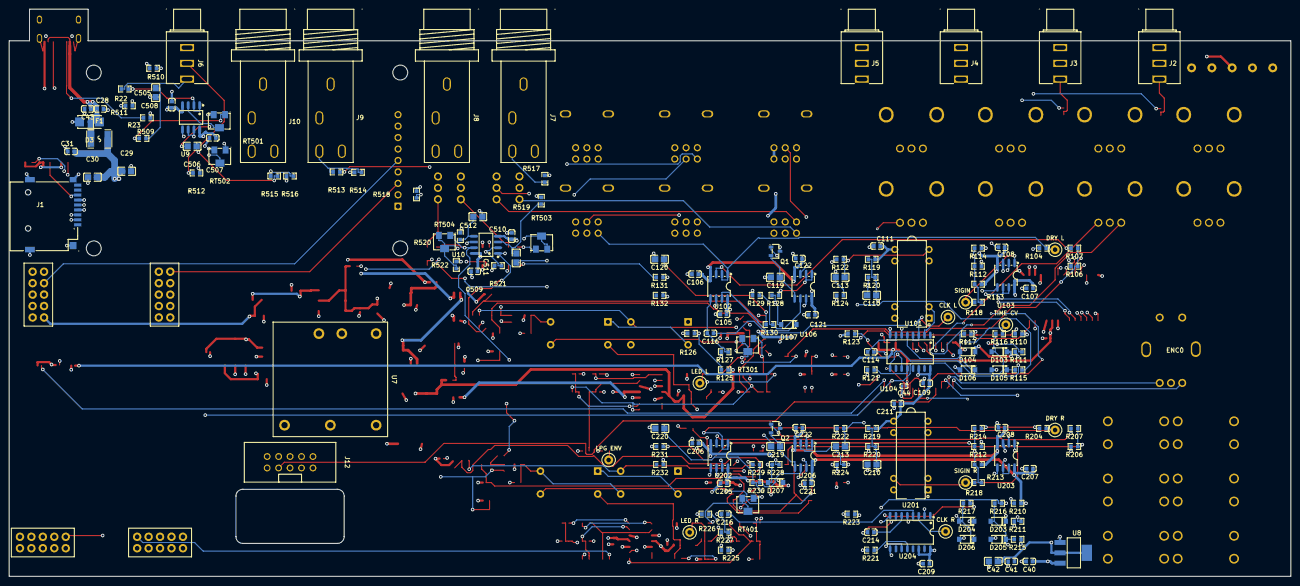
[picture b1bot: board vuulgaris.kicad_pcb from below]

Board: 4 copper layers, 284.3 x 125.8 mm, 321 parts (168 on the bottom side), 222 nets.

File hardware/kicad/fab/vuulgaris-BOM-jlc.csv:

Comment,Designator,Footprint,LCSC Part #
0402WGF2201TCE,"R20,R21",R0402,C25879
"0R  (IN GAIN -- OPEN, see docs/bbd-mki.md)","R104,R204",R0603,C21189
100k,"R106,R115,R116,R117,R122,R124,R125,R128,R130,R206,R215,R216,R217,R222,R224,R225,R228,R230,R305,R309,R310,R317,R318,R320,R323,R328,R330,R331,R333,R405,R409,R410,R417,R418,R420,R423,R428,R430,R431,R433,R509,R510,R519,R520",R0603,C25803
100nF / CC0603JRX7R8BB104,"C31,C34,C35,C38,C39,C40,C41,C43,C105,C106,C107,C108,C109,C111,C121,C122,C205,C206,C207,C208,C209,C211,C221,C222,C301,C302,C303,C304,C401,C402,C403,C404,C507,C508,C509,C510",C0603,C14663
10k,"R118,R126,R218,R226,R301,R302,R308,R314,R401,R402,R408,R414,R505",R0603,C25804
10nF C0G 0805,"C119,C219",C0805,C237168
10uF / CL21A106KAYNNNE,"C20,C22,C24,C25,C29,C42,C110,C210",C0805,C15850
12x12 tactile,"SW4,SW5,SW6,SW7,SW8,SW9",KEY-TH_4P-L12.0-W12.0-P5.00-LS12.5,C54573007
150k,"R303,R403",R0603,C22807
15k,"R311,R312,R411,R412",R0603,C22809
1M,"R501,R502",R0603,C22935
1N4148W,"D103,D104,D105,D106,D107,D203,D204,D205,D206,D207,D302,D402",SOD-123_L2.8-W1.8-LS3.7-RD,C81598
1k,"R107,R207,R315,R415,R503,R504,R514,R516,R517,R518",R0603,C21190
1k2,"R513,R515",R0603,C22765
1nF C0G,"C114,C214,C309,C409",C0603,C163508
1uF X7R 50V / CC0805KKX7R9BB105,"C30,C113,C120,C213,C220,C306,C406,C501,C502,C503,C504,C505,C506,C511,C512",C0805,C28323
2.2M,"R121,R221,R334,R434",R0603,C22938
20k trim,"RT301,RT401,RT501,RT502,RT503,RT504",RES-ADJ-SMD_3224W,C55071
220pF C0G,"C116,C216,C307,C407",C0603,C27675
22k,"R110,R111,R129,R210,R211,R229",R0603,C31850
22pF C0G,"C310,C410",C0603,C1653
2k2,"R521,R522",R0603,C4190
2nF C0G,"C305,C405",C0603,C296055
33k,"R307,R407",R0603,C4216
39k,"R123,R223",R0603,C23153
3V9 zener,"D301,D401",SOD-123_L2.7-W1.6-LS3.7-RD-1,C213113
4.7k,"R119,R219",R0603,C23162
4.7nF C0G,"C308,C408",C0603,C576818
470R,"R131,R132,R231,R232,R306,R406",R0603,C23179
470k,"R304,R404",R0603,C23178
47k,"R113,R213,R506,R507,R508",R0603,C25819
4M7,"R313,R413",R0603,C23163
4R7,"R511,R512",R0603,C23164
51k,"R114,R214",R0603,C23196
6.2k,"R127,R227",R0603,C4260
62k,"R120,R220",R0603,C23221
82k,"R112,R212",R0603,C23254
AMS1117-3.3,"U5,U6",SOT-223-3_L6.5-W3.4-P2.30-LS7.0-BR,C6186
AMS1117-5.0,U8,SOT-223-3_L6.5-W3.4-P2.30-LS7.0-BR,C6187
ASMD1812-300,F1,F1812,C135366
BEAD0805S601A20T,"FB1,FB2",R0805,C1017
BLM18PG121SN1D_C14709,"L1,L2",L0603,C14709
CC0603JRNPO9BN103,C28,C0603,C57112
CD4046B,"U104,U204",SO-16_L10.3-W5.3-P1.27-LS7.8-BL,C2651237
CL05B104KO5NNNC,"C21,C23,C26,C27,C44",C0402,C1525
CUTOFF / FILTER CV AMT / RESONANCE / TIME / WET/DRY,"RV1,RV2,RV3,RV4,RV6",RES-ADJ-TH_RK09L1240A12,
DKM10E-12,U7,PWRM-TH_DKMW30F-12,
EC11L1525G01,ENC0,SW-TH_ALPS_EC11L1525G01,C2991196
EC12E2430803,"ENC1,ENC2,ENC3,ENC4,ENC5,ENC6,ENC7,ENC8",SW-TH_EC12EXXXX,C470684
ES_DAISY_PATCH_SM_REV1,U1,DAISY_PATCH_SM,
FACEPLATE 2x5 IDC,J12,IDC-TH_10P-P2.54_C5665,C5665
FEEDBACK,RV5,RES-ADJ-TH_RK09L1240A12,
HS242L01W4S01,DS1,LCD-TH_HS242L01W4S01,
J113 / MMBFJ113,"Q1,Q2",SOT-23-3_L2.9-W1.3-P1.90-LS2.4-BR,C891686
MCP23017-E_SO,"U3,U4",SOIC-28_L18.0-W7.5-P1.27-LS10.3-BL,C47023
OPA1688_FLAT,"U9,U10",SOP-8_L4.9-W3.9-P1.27-LS6.0-BL,C206212
PJ-376,"J2,J3,J4,J5,J6",AUDIO-TH_PJ-376,C22355746
PJ-603_C41409498,"J7,J8,J9,J10",AUDIO-TH_PJ-603,C41409498
RT0603BRD072K2L,"R24,R25",R0603,C861295
RT0603BRD075K1L,"R22,R23",R0603,C122969
RVT1E470M0505_C2977553,"C32,C33",CAP-SMD_BD5.0-L5.3-W5.3-LS6.3-FD,C2977553
RVT1H220M0605,"C36,C37",CAP-SMD_BD6.3-L6.6-W6.6-FD,C72505
SMAJ6.0A,D3,SMA_L4.3-W2.6-LS5.2-RD,C223993
SW_DPDT_FLAT,"SW1,SW2",SW-TH_DW3_DPDT_2MD1T1B1M2QES,
TFPUSH,J1,TF-SMD_TF-PUSH,C393941
TL072_FLAT,"U102,U103,U106,U202,U203,U206",SOIC-8_L4.9-W3.9-P1.27-LS6.1-BL,C67473
TL074,"U302,U402",SOIC-14_3.9x8.7mm_P1.27mm,C12594
TL084,"U301,U401",SOIC-14_3.9x8.7mm_P1.27mm,C8956
TYPE-C-31-M-12,J11,USB-C_SMD-TYPE-C-31-M-12_1,C165948
V3205SD,"U101,U201",DIP-8_SPECIAL_V3205SD,
VTL5C3,"VT301,VT302,VT401,VT402",VACTROL-TH_VTL5C3,
YLED0402Y,"D1,D2",LED0402-R-RD,C20608782
